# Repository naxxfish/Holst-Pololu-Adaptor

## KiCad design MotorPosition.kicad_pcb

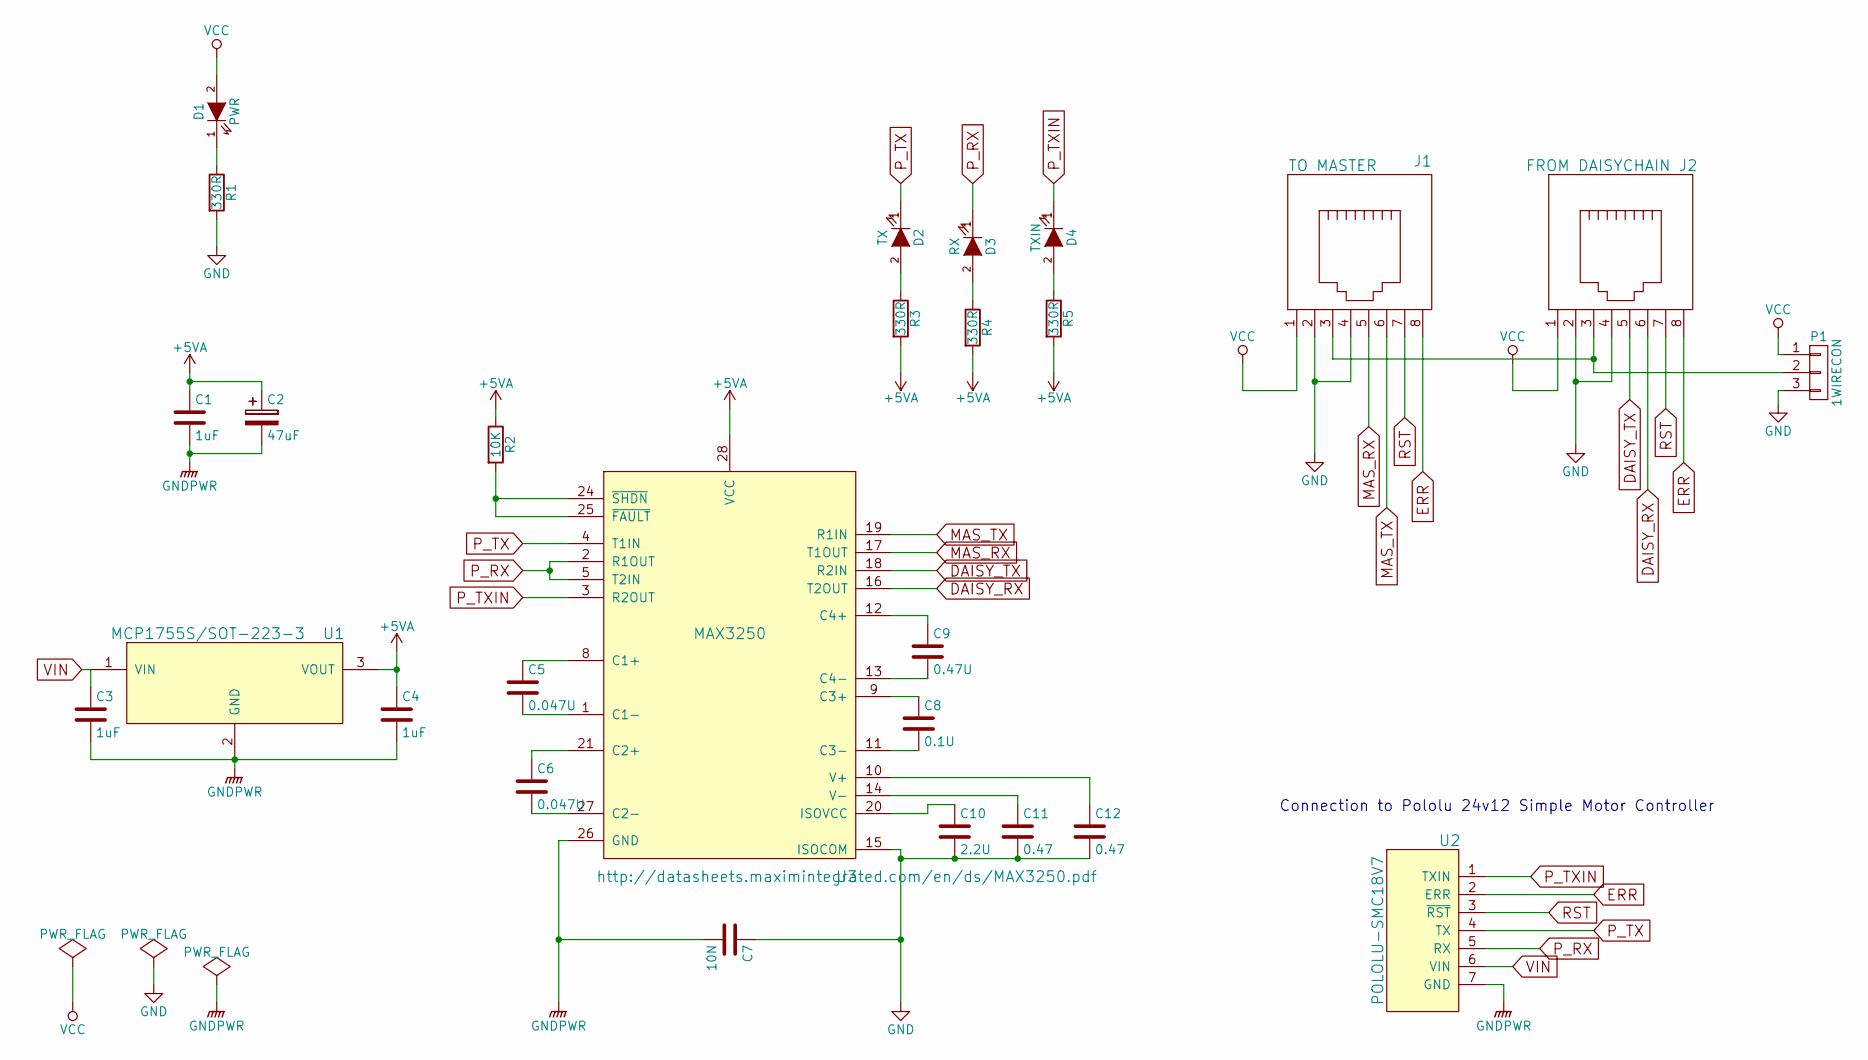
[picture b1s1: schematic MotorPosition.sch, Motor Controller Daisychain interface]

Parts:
C1, C3, C4: 1uF; C_0805
C2: 47uF; Elko_vert_11x5mm_RM2
C5, C6: 0.047U; C_0805
C7: 10N; C_0603_HandSoldering
C8: 0.1U; C_0603_HandSoldering
C9: 0.47U; C_0603_HandSoldering
C10: 2.2U; C_0805
C11, C12: 0.47; C_0805
D1: PWR; LED-3MM
D2: TX; LED-3MM
D3: RX; LED-3MM
D4: TXIN; LED-3MM
J1: TO MASTER; RJ45-RJSE-5080-ND
J2: FROM DAISYCHAIN; RJ45-RJSE-5080-ND
P1: 1WIRECON; PINHEAD1-3
R1, R3, R4, R5: 330R; R_0805
R2: 10K; R_0805
U1: MCP1755S/SOT-223-3; SOT-223-3
U2: POLOLU-SMC18V7; POLOLU-18V15
U3: MAX3250; MAXIM-SSOP28

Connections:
+5VA: C1.1, C2.1, C4.1, R2.1, R3.2, R4.2, R5.2, U1.3 (VOUT), U3.28 (VCC)
DAISY_RX: J2.6, U3.16 (T2OUT)
DAISY_TX: J2.5, U3.18 (R2IN)
ERR: J1.8, J2.8, U2.2 (ERR)
GND: C7.1, C10.2, C11.2, C12.2, J1.2, J1.4, J2.2, J2.4, P1.3, R1.2, U3.15 (ISOCOM)
GNDPWR: C1.2, C2.2, C3.2, C4.2, C7.2, U1.2 (GND), U2.7 (GND), U3.26 (GND)
MAS_RX: J1.5, U3.17 (T1OUT)
MAS_TX: J1.6, U3.19 (R1IN)
unnamed: C5.1, U3.8 (C1+)
unnamed: C5.2, U3.1 (C1-)
unnamed: C6.1, U3.21 (C2+)
unnamed: C6.2, U3.27 (C2-)
unnamed: C8.1, U3.9 (C3+)
unnamed: C8.2, U3.11 (C3-)
unnamed: C9.1, U3.12 (C4+)
unnamed: C9.2, U3.13 (C4-)
unnamed: C10.1, U3.20 (ISOVCC)
unnamed: C11.1, U3.14 (V-)
unnamed: C12.1, U3.10 (V+)
unnamed: D1.1 (K), R1.1
unnamed: D2.2 (A), R3.1
unnamed: D3.2 (A), R4.1
unnamed: D4.2 (A), R5.1
unnamed: J1.3, J2.3, P1.2
unnamed: R2.2, U3.24 (~SHDN), U3.25 (~FAULT)
P_RX: D3.1 (K), U2.5 (RX), U3.2 (R1OUT), U3.5 (T2IN)
P_TX: D2.1 (K), U2.4 (TX), U3.4 (T1IN)
P_TXIN: D4.1 (K), U2.1 (TXIN), U3.3 (R2OUT)
RST: J1.7, J2.7, U2.3 (~RST)
VCC: D1.2 (A), J1.1, J2.1, P1.1
VIN: C3.1, U1.1 (VIN), U2.6 (VIN)

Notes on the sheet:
Connection to Pololu 24v12 Simple Motor Controller

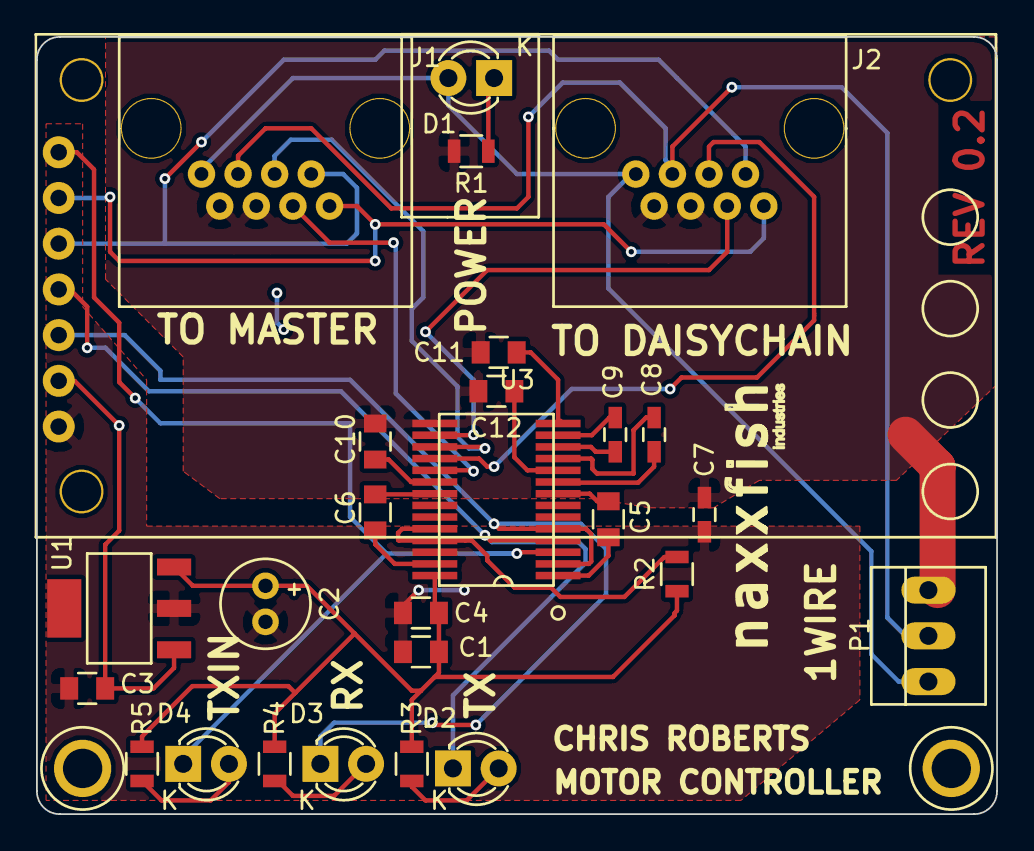
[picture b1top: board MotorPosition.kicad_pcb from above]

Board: 2 copper layers, 53.3 x 43.2 mm, 27 parts (0 on the bottom side), 31 nets.
